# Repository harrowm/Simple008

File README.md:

Aim is to create a very simple 68008 computer on a 10cm square PCB so thats its low cost.  Hopefully make the SBC capable of running the rosco sbc firmware .. for that reason it will need 512Kb of ROM and 1Mb of RAM.

Here's a picture of v1 ..

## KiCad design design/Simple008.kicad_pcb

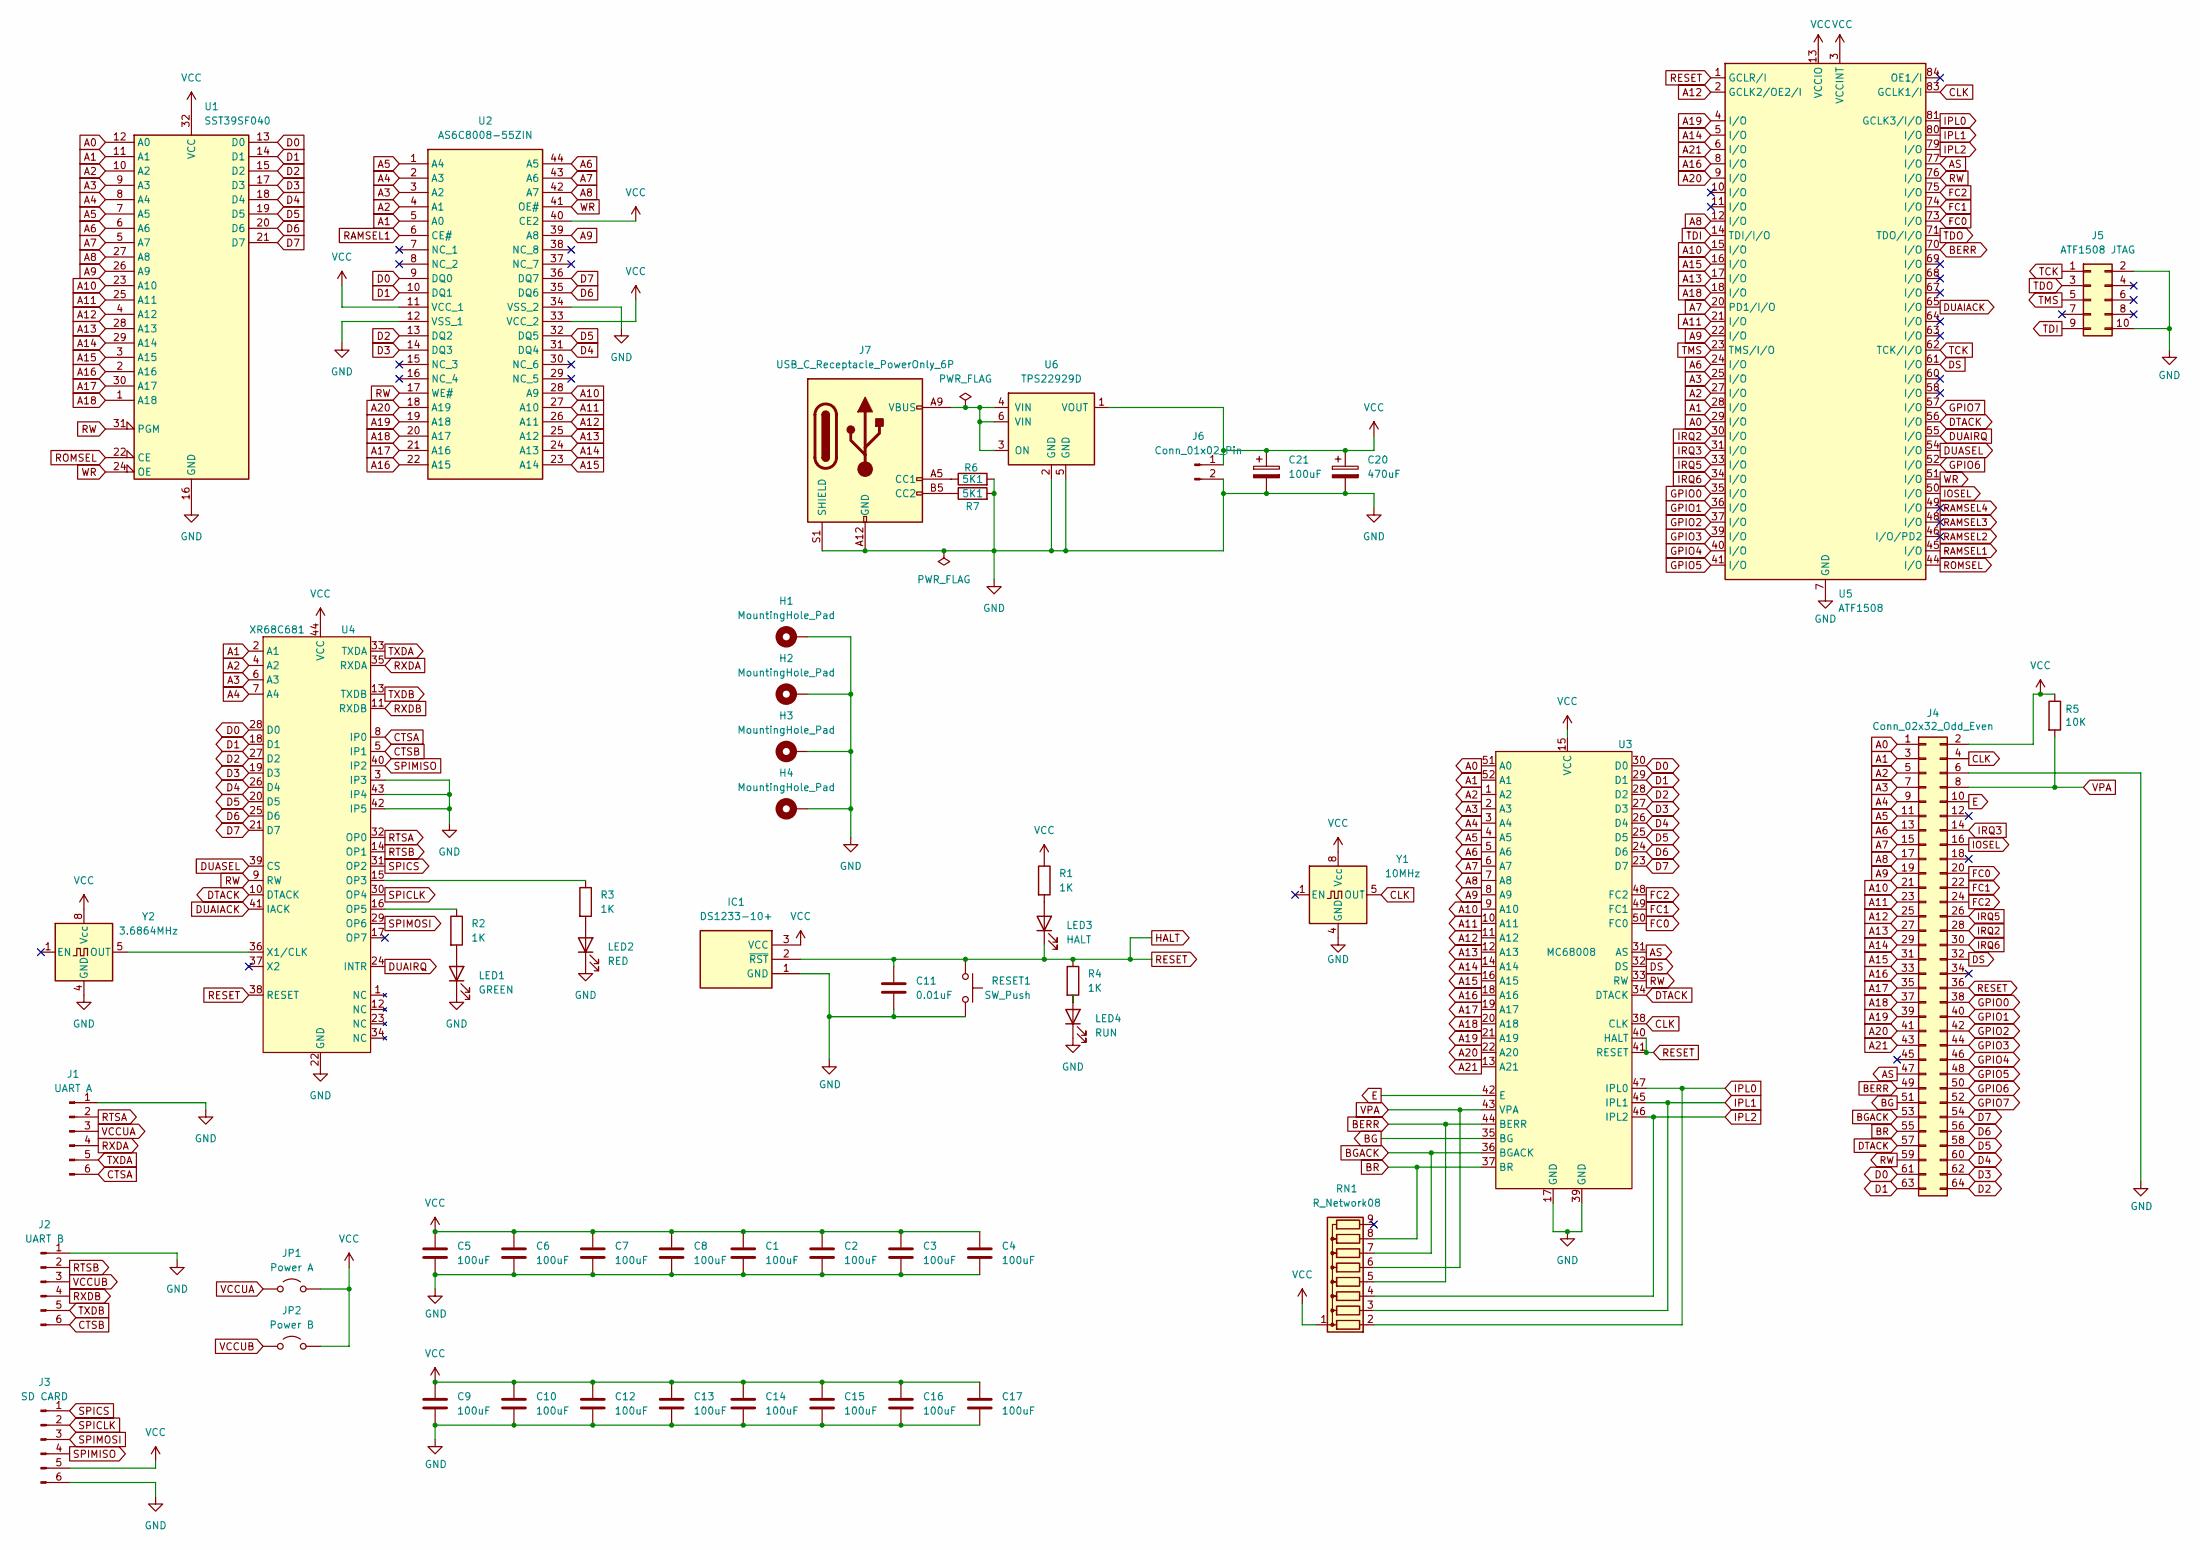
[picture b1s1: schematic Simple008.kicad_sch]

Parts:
C1, C2, C3, C4, C5, C6, C7, C8, C9, C10, C12, C13, C14, C15, C16, C17: 100uF; C_0805_2012Metric_Pad1.18x1.45mm_HandSolder
C11: 0.01uF; C_0805_2012Metric_Pad1.18x1.45mm_HandSolder
C20: 470uF; CP_Radial_D10.0mm_P3.50mm
C21: 100uF; CP_Radial_D5.0mm_P2.50mm
H1, H2, H3, H4: MountingHole_Pad; MountingHole_3.2mm_M3_Pad_Via
IC1: DS1233-10+; TO-92_HandSolder; Mouser Part Number 700-DS1233-10
J1: UART A; PinHeader_1x06_P2.54mm_Vertical
J2: UART B; PinHeader_1x06_P2.54mm_Vertical
J3: SD CARD; PinHeader_1x06_P2.54mm_Vertical
J4: Conn_02x32_Odd_Even; PinHeader_2x32_P2.54mm_Vertical
J5: ATF1508 JTAG; IDC-Header_2x05_P2.54mm_Vertical
J6: Conn_01x02_Pin; PinHeader_1x02_P2.54mm_Vertical
J7: USB_C_Receptacle_PowerOnly_6P; USB_C_Receptacle_GCT_USB4125-xx-x_6P_TopMnt_Horizontal
JP1: Power A; PinHeader_1x02_P2.54mm_Vertical
JP2: Power B; PinHeader_1x02_P2.54mm_Vertical
LED1: GREEN; LED_0805_2012Metric_Pad1.15x1.40mm_HandSolder
LED2: RED; LED_0805_2012Metric_Pad1.15x1.40mm_HandSolder
LED3: HALT; LED_0805_2012Metric_Pad1.15x1.40mm_HandSolder
LED4: RUN; LED_0805_2012Metric_Pad1.15x1.40mm_HandSolder
R1, R2, R3, R4: 1K; R_0805_2012Metric_Pad1.20x1.40mm_HandSolder
R5: 10K; R_0805_2012Metric_Pad1.20x1.40mm_HandSolder
R6, R7: 5K1; R_0805_2012Metric_Pad1.20x1.40mm_HandSolder
RESET1: SW_Push; SW_TH_Tactile_Omron_B3F-10xx
RN1: R_Network08; R_Array_SIP9
U1: SST39SF040; DIP-32_W15.24mm_Socket_LongPads
U2: AS6C8008-55ZIN; TSOP-II-44_10.16x18.41mm_P0.8mm; Manufacturer_Part_Number AS6C8008-55ZIN; Mouser Part Number 913-AS6C8008-55ZIN
U3: MC68008; PLCC-52_THT-Socket
U4: XR68C681; PLCC-44_THT-Socket
U5: ATF1508; PLCC-84_THT-Socket
U6: TPS22929D; SOT-23-6
Y1: 10MHz; Oscillator_DIP-8
Y2: 3.6864MHz; Oscillator_DIP-8

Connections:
A0: J4.1, U1.12 (A0), U3.51 (A0), U5.29 (I/O)
A1: J4.3, U1.11 (A1), U2.5 (A0), U3.52 (A1), U4.2 (A1), U5.28 (I/O)
A2: J4.5, U1.10 (A2), U2.4 (A1), U3.1 (A2), U4.4 (A2), U5.27 (I/O)
A3: J4.7, U1.9 (A3), U2.3 (A2), U3.2 (A3), U4.6 (A3), U5.25 (I/O)
A4: J4.9, U1.8 (A4), U2.2 (A3), U3.3 (A4), U4.7 (A4)
A5: J4.11, U1.7 (A5), U2.1 (A4), U3.4 (A5)
A6: J4.13, U1.6 (A6), U2.44 (A5), U3.5 (A6), U5.24 (I/O)
A7: J4.15, U1.5 (A7), U2.43 (A6), U3.6 (A7), U5.20 (PD1/I/O)
A8: J4.17, U1.27 (A8), U2.42 (A7), U3.7 (A8), U5.12 (I/O)
A9: J4.19, U1.26 (A9), U2.39 (A8), U3.8 (A9), U5.22 (I/O)
A10: J4.21, U1.23 (A10), U2.28 (A9), U3.9 (A10), U5.15 (I/O)
A11: J4.23, U1.25 (A11), U2.27 (A10), U3.10 (A11), U5.21 (I/O)
A12: J4.25, U1.4 (A12), U2.26 (A11), U3.11 (A12), U5.2 (GCLK2/OE2/I)
A13: J4.27, U1.28 (A13), U2.25 (A12), U3.12 (A13), U5.17 (I/O)
A14: J4.29, U1.29 (A14), U2.24 (A13), U3.14 (A14), U5.5 (I/O)
A15: J4.31, U1.3 (A15), U2.23 (A14), U3.16 (A15), U5.16 (I/O)
A16: J4.33, U1.2 (A16), U2.22 (A15), U3.18 (A16), U5.8 (I/O)
A17: J4.35, U1.30 (A17), U2.21 (A16), U3.19 (A17)
A18: J4.37, U1.1 (A18), U2.20 (A17), U3.20 (A18), U5.18 (I/O)
A19: J4.39, U2.19 (A18), U3.21 (A19), U5.4 (I/O)
A20: J4.41, U2.18 (A19), U3.22 (A20), U5.9 (I/O)
A21: J4.43, U3.13 (A21), U5.6 (I/O)
AS: J4.47, U3.31 (AS), U5.77 (I/O)
BERR: J4.49, RN1.5 (R4), U3.44 (BERR), U5.70 (I/O)
BG: J4.51, U3.35 (BG)
BGACK: J4.53, RN1.7 (R6), U3.36 (BGACK)
BR: J4.55, RN1.8 (R7), U3.37 (BR)
CLK: J4.4, U3.38 (CLK), U5.83 (GCLK1/I), Y1.5 (OUT)
CTSA: J1.6, U4.8 (IP0)
CTSB: J2.6, U4.5 (IP1)
D0: J4.61, U1.13 (D0), U2.9 (DQ0), U3.30 (D0), U4.28 (D0)
D1: J4.63, U1.14 (D1), U2.10 (DQ1), U3.29 (D1), U4.18 (D1)
D2: J4.64, U1.15 (D2), U2.13 (DQ2), U3.28 (D2), U4.27 (D2)
D3: J4.62, U1.17 (D3), U2.14 (DQ3), U3.27 (D3), U4.19 (D3)
D4: J4.60, U1.18 (D4), U2.31 (DQ4), U3.26 (D4), U4.26 (D4)
D5: J4.58, U1.19 (D5), U2.32 (DQ5), U3.25 (D5), U4.20 (D5)
D6: J4.56, U1.20 (D6), U2.35 (DQ6), U3.24 (D6), U4.25 (D6)
D7: J4.54, U1.21 (D7), U2.36 (DQ7), U3.23 (D7), U4.21 (D7)
DS: J4.32, U3.32 (DS), U5.61 (I/O)
DTACK: J4.57, U3.34 (DTACK), U4.10 (DTACK), U5.56 (I/O)
DUAIACK: U4.41 (IACK), U5.65 (I/O)
DUAIRQ: U4.24 (INTR), U5.55 (I/O)
DUASEL: U4.39 (CS), U5.54 (I/O)
E: J4.10, U3.42 (E)
FC0: J4.20, U3.50 (FC0), U5.73 (I/O)
FC1: J4.22, U3.49 (FC1), U5.74 (I/O)
FC2: J4.24, U3.48 (FC2), U5.75 (I/O)
GND: C1.2, C2.2, C3.2, C4.2, C5.2, C6.2, C7.2, C8.2, C9.2, C10.2, C11.2, C12.2, C13.2, C14.2, C15.2, C16.2, C17.2, C20.2, C21.2, H1.1, H2.1, H3.1, H4.1, IC1.1 (GND), J1.1, J2.1, J3.6, J4.6, J5.2, J5.10, J6.2, J7.A12 (GND), J7.B12 (GND), J7.S1 (SHIELD), LED1.1 (K), LED2.1 (K), LED4.1 (K), R6.2, R7.2, RESET1.1, U1.16 (GND), U2.12 (VSS_1), U2.34 (VSS_2), U3.17 (GND), U3.39 (GND), U4.3 (IP3), U4.22 (GND), U4.42 (IP5), U4.43 (IP4), U5.7 (GND), U5.19 (GND), U5.32 (GND), U5.42 (GND), U5.47 (GND), U5.59 (GND), U5.72 (GND), U5.82 (GND), U6.2 (GND), U6.5 (GND), Y1.4 (GND), Y2.4 (GND); also elsewhere on the board
GPIO0: J4.38, U5.35 (I/O)
GPIO1: J4.40, U5.36 (I/O)
GPIO2: J4.42, U5.37 (I/O)
GPIO3: J4.44, U5.39 (I/O)
GPIO4: J4.46, U5.40 (I/O)
GPIO5: J4.48, U5.41 (I/O)
GPIO6: J4.50, U5.52 (I/O)
GPIO7: J4.52, U5.57 (I/O)
HALT: C11.1, IC1.2 (~RST), J4.36, LED3.1 (K), R4.1, RESET1.2, U3.40 (HALT), U3.41 (RESET), U4.38 (RESET), U5.1 (GCLR/I); also elsewhere on the board
IOSEL: J4.16, U5.50 (I/O)
IPL0: RN1.2 (R1), U3.47 (IPL0), U5.81 (GCLK3/I/O)
IPL1: RN1.3 (R2), U3.45 (IPL1), U5.80 (I/O)
IPL2: RN1.4 (R3), U3.46 (IPL2), U5.79 (I/O)
IRQ2: J4.28, U5.30 (I/O)
IRQ3: J4.14, U5.31 (I/O)
IRQ5: J4.26, U5.33 (I/O)
IRQ6: J4.30, U5.34 (I/O)
unnamed: J7.A5 (CC1), R6.1
unnamed: J7.B5 (CC2), R7.1
unnamed: LED1.2 (A), R2.2
unnamed: LED2.2 (A), R3.2
unnamed: LED3.2 (A), R1.2
unnamed: LED4.2 (A), R4.2
unnamed: R3.1, U4.15 (OP3)
unnamed: R2.1, U4.16 (OP5)
unnamed: U4.36 (X1/CLK), Y2.5 (OUT)
unnamed: J7.A9 (VBUS), J7.B9 (VBUS), U6.3 (ON), U6.4 (VIN), U6.6 (VIN)
RAMSEL1: U2.6 (CE#), U5.45 (I/O)
RAMSEL2: U5.46 (I/O/PD2)
RAMSEL3: U5.48 (I/O)
RAMSEL4: U5.49 (I/O)
ROMSEL: U1.22 (CE), U5.44 (I/O)
RTSA: J1.2, U4.32 (OP0)
RTSB: J2.2, U4.14 (OP1)
RW: J4.59, U1.31 (PGM), U2.17 (WE#), U3.33 (RW), U4.9 (RW), U5.76 (I/O)
RXDA: J1.4, U4.35 (RXDA)
RXDB: J2.4, U4.11 (RXDB)
SPICLK: J3.2, U4.30 (OP4)
SPICS: J3.1, U4.31 (OP2)
SPIMISO: J3.4, U4.40 (IP2)
SPIMOSI: J3.3, U4.29 (OP6)
TCK: J5.1, U5.62 (TCK/I/O)
TDI: J5.9, U5.14 (TDI/I/O)
TDO: J5.3, U5.71 (TDO/I/O)
TMS: J5.5, U5.23 (TMS/I/O)
TXDA: J1.5, U4.33 (TXDA)
TXDB: J2.5, U4.13 (TXDB)
VCC: C1.1, C2.1, C3.1, C4.1, C5.1, C6.1, C7.1, C8.1, C9.1, C10.1, C12.1, C13.1, C14.1, C15.1, C16.1, C17.1, C20.1, C21.1, IC1.3 (VCC), J3.5, J4.2, J6.1, JP1.2 (B), JP2.2 (B), R1.1, R5.1, RN1.1 (common), U1.32 (VCC), U2.11 (VCC_1), U2.33 (VCC_2), U2.40 (CE2), U3.15 (VCC), U4.44 (VCC), U5.3 (VCCINT), U5.13 (VCCIO), U5.26 (VCCIO), U5.38 (VCCIO), U5.43 (VCCINT), U5.53 (VCCIO), U5.66 (VCCIO), U5.78 (VCCIO), U6.1 (VOUT), Y1.8 (Vcc), Y2.8 (Vcc)
VCCUA: J1.3, JP1.1 (A)
VCCUB: J2.3, JP2.1 (A)
VPA: J4.8, R5.2, RN1.6 (R5), U3.43 (VPA)
WR: U1.24 (OE), U2.41 (OE#), U5.51 (I/O)

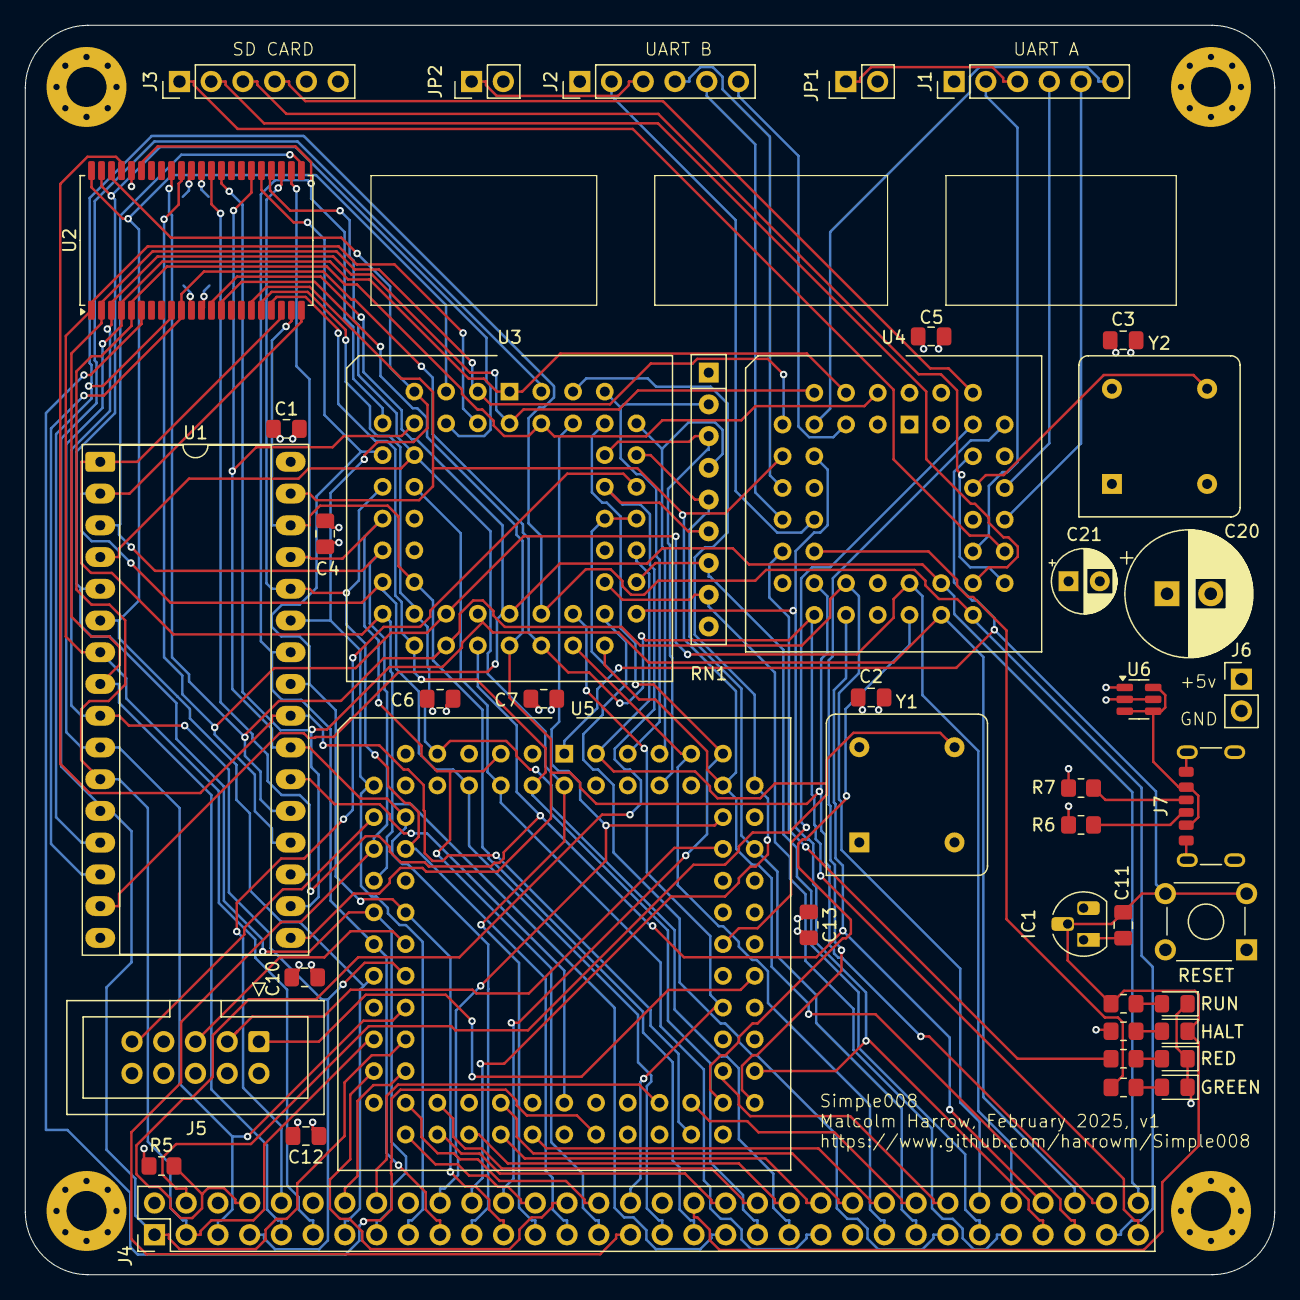
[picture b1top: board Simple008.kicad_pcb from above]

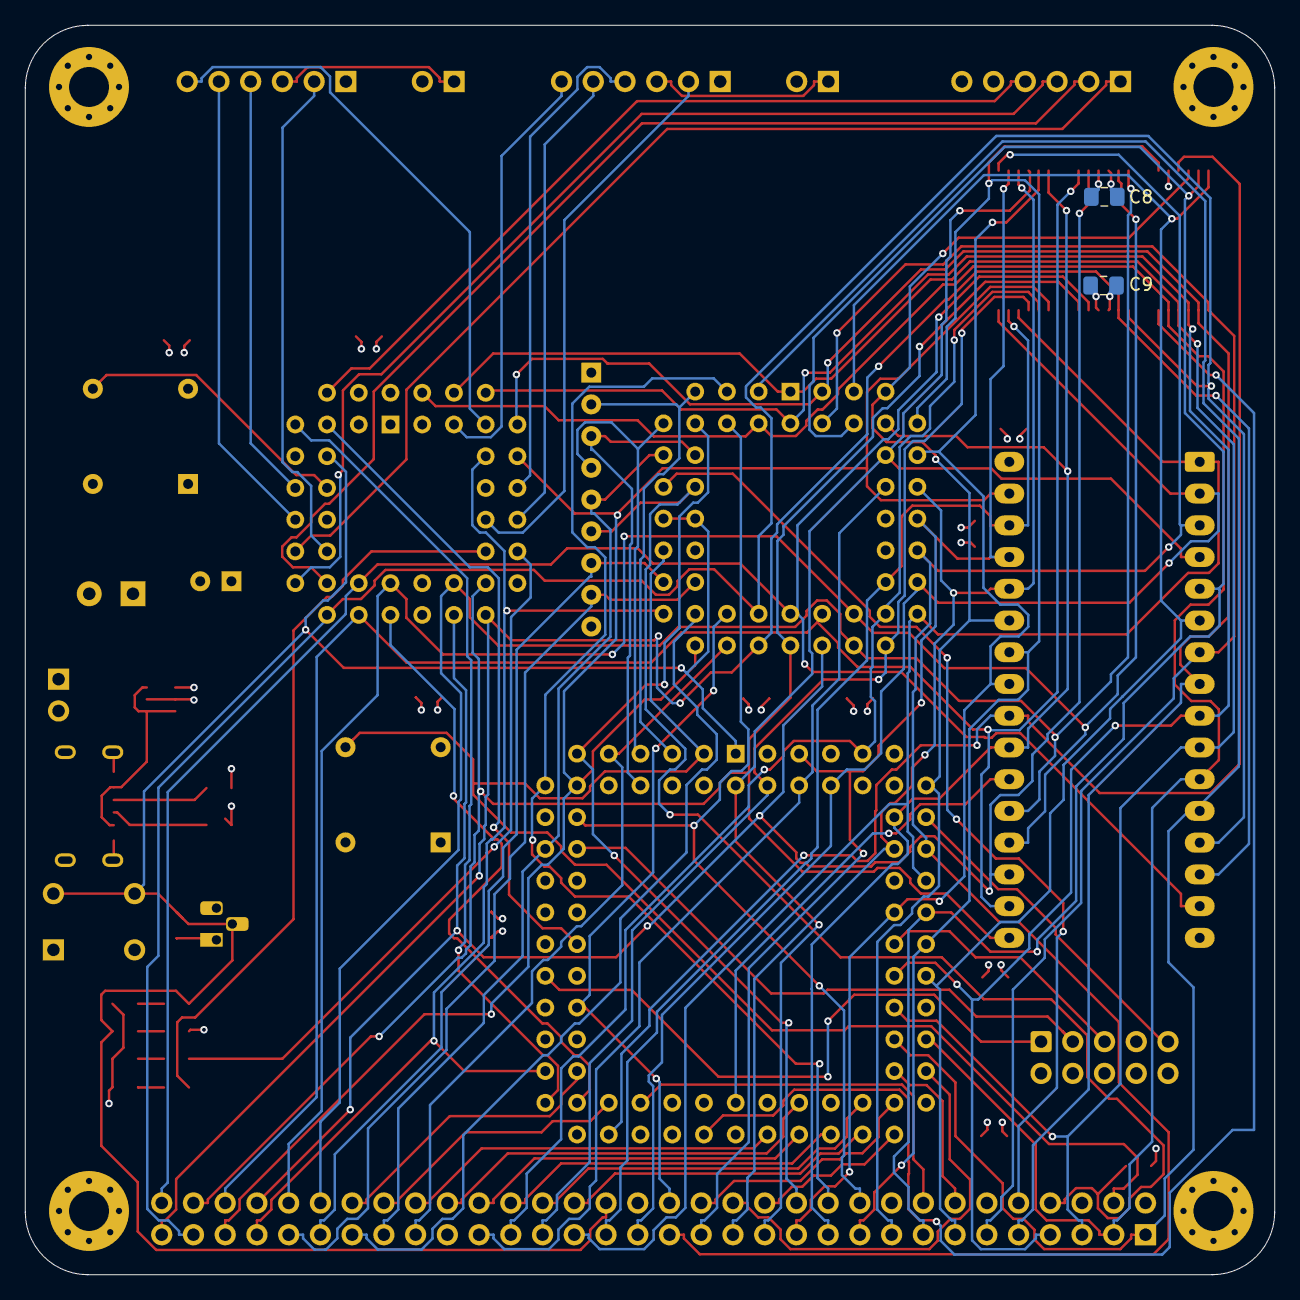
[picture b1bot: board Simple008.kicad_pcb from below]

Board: 4 copper layers, 100.0 x 100.0 mm, 50 parts (2 on the bottom side), 97 nets.

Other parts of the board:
RESET: SW_Push; SW_TH_Tactile_Omron_B3F-10xx

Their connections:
GND: RESET.1; also elsewhere on the board
HALT: RESET.2; also elsewhere on the board

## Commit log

2025-02-13 First cut Kicad design
2025-02-16 PCB layout component positioning
2025-02-16 Add DS_Store to .gitignore
2025-02-18 Initial board routing
2025-02-18 Clean ERC
2025-02-25 Fabrication
2025-03-09 Include production files
2025-03-09 Add photo of v1 baord
2025-03-10 Start of pld and firmware
2025-03-10 First pld program
2025-03-14 Working on PLD
